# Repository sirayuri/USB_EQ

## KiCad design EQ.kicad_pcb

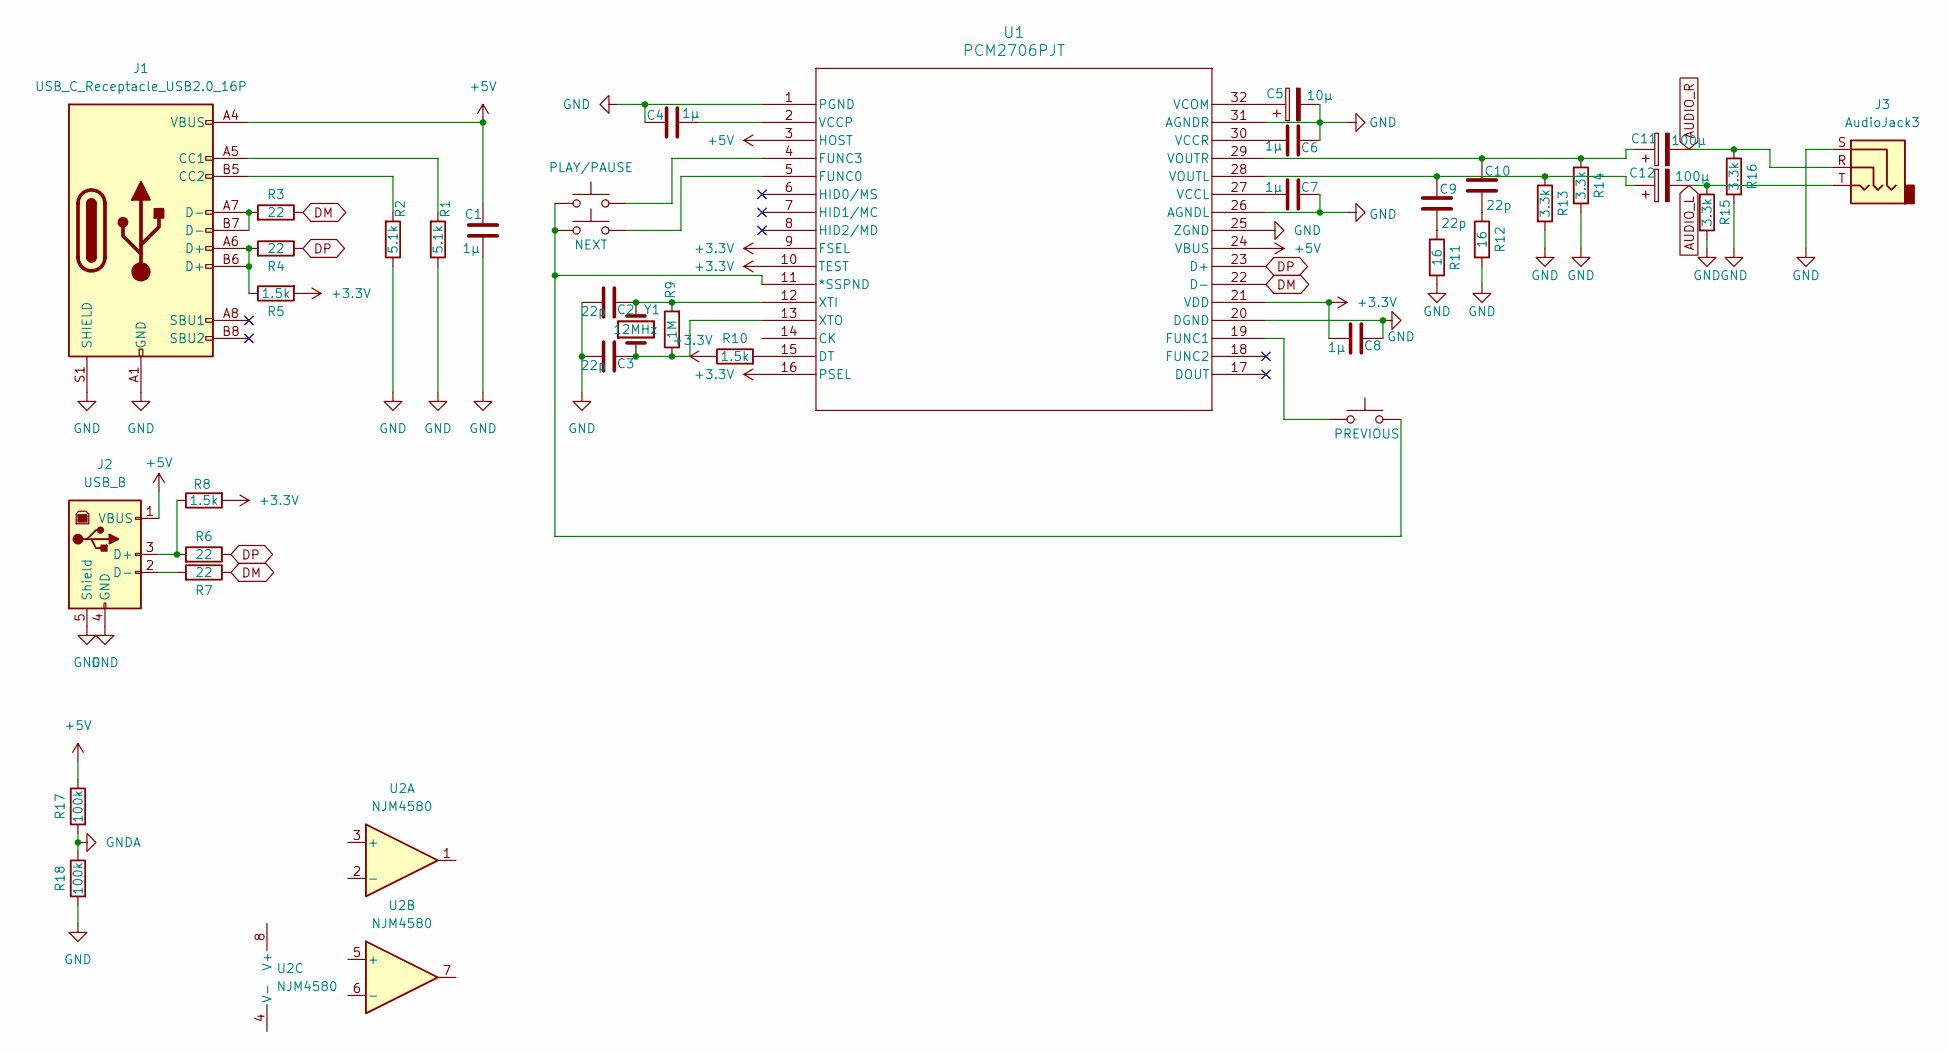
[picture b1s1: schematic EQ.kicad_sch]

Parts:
C1, C4, C6, C7, C8: 1μ; C_0603_1608Metric_Pad1.08x0.95mm_HandSolder
C2, C3, C9, C10: 22p; C_0603_1608Metric_Pad1.08x0.95mm_HandSolder
C5: 10μ; CP_Radial_D5.0mm_P2.50mm
C11, C12: 100μ; CP_Radial_D10.0mm_P3.50mm
J1: USB_C_Receptacle_USB2.0_16P; USB_C_Receptacle_HRO_TYPE-C-31-M-12
J2: USB_B; USB_B_Lumberg_2411_02_Horizontal
J3: AudioJack3; Jack_3.5mm_Lumberg_1503_07_Horizontal
R1, R2: 5.1k; R_0603_1608Metric_Pad0.98x0.95mm_HandSolder
R3, R4, R6, R7: 22; R_0603_1608Metric_Pad0.98x0.95mm_HandSolder
R5, R8, R10: 1.5k; R_0603_1608Metric_Pad0.98x0.95mm_HandSolder
R9: 1M; R_0603_1608Metric_Pad0.98x0.95mm_HandSolder
R11, R12: 16; R_0603_1608Metric_Pad0.98x0.95mm_HandSolder
R13, R14, R15, R16: 3.3k; R_0603_1608Metric_Pad0.98x0.95mm_HandSolder
R17, R18: 100k; R_0603_1608Metric_Pad0.98x0.95mm_HandSolder
SW1: PLAY/PAUSE; SW_PUSH_6mm
SW2: NEXT; SW_PUSH_6mm
SW3: PREVIOUS; SW_PUSH_6mm
U1: PCM2706PJT; PJT32
U2: NJM4580; SOIC-8_3.9x4.9mm_P1.27mm
Y1: 12MHz; Crystal_HC18-U_Vertical

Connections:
+3.3V: C8.2, R5.2, R8.2, R10.1, U1.9 (FSEL), U1.10 (TEST), U1.16 (PSEL), U1.21 (VDD)
+5V: C1.1, J1.A4 (VBUS), J1.A9 (VBUS), J1.B4 (VBUS), J1.B9 (VBUS), J2.1 (VBUS), R17.1, U1.3 (HOST), U1.24 (VBUS)
AUDIO_L: C12.2, J3.T, R15.1
AUDIO_R: C11.2, J3.R, R16.1
DM: R3.1, R7.1, U1.22 (D-)
DP: R4.1, R6.1, U1.23 (D+)
GND: C1.2, C2.2, C3.2, C4.1, C5.2, C6.1, C7.1, C8.1, J1.A1 (GND), J1.A12 (GND), J1.B1 (GND), J1.B12 (GND), J1.S1 (SHIELD), J2.4 (GND), J2.5 (Shield), J3.S, R1.1, R2.1, R11.2, R12.2, R13.2, R14.2, R15.2, R16.2, R18.2, U1.1 (PGND), U1.20 (DGND), U1.25 (ZGND), U1.26 (AGNDL), U1.31 (AGNDR)
GNDA: R17.2, R18.1
unnamed: C9.2, R11.1
unnamed: C10.2, R12.1
unnamed: J1.A5 (CC1), R1.2
unnamed: J1.B5 (CC2), R2.2
unnamed: J1.A6 (D+), J1.B6 (D+), R4.2, R5.1
unnamed: J1.A7 (D-), J1.B7 (D-), R3.2
unnamed: J2.3 (D+), R6.2, R8.1
unnamed: J2.2 (D-), R7.2
unnamed: SW1.1, SW2.1, SW3.2, U1.11 (*SSPND)
unnamed: R10.2, U1.15 (DT)
unnamed: SW2.2, U1.5 (FUNC0)
unnamed: SW3.1, U1.19 (FUNC1)
unnamed: SW1.2, U1.4 (FUNC3)
unnamed: C7.2, U1.27 (VCCL)
unnamed: C4.2, U1.2 (VCCP)
unnamed: C6.2, U1.30 (VCCR)
unnamed: C5.1, U1.32 (VCOM)
unnamed: C9.1, C12.1, R13.1, U1.28 (VOUTL)
unnamed: C10.1, C11.1, R14.1, U1.29 (VOUTR)
unnamed: C2.1, R9.2, U1.12 (XTI), Y1.2
unnamed: C3.1, R9.1, U1.13 (XTO), Y1.1

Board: 2 copper layers, 39 parts (0 on the bottom side), 29 nets, no tracks yet.

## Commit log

2025-06-08 FirstCommit
2025-06-08 OPampを回路図に配置
